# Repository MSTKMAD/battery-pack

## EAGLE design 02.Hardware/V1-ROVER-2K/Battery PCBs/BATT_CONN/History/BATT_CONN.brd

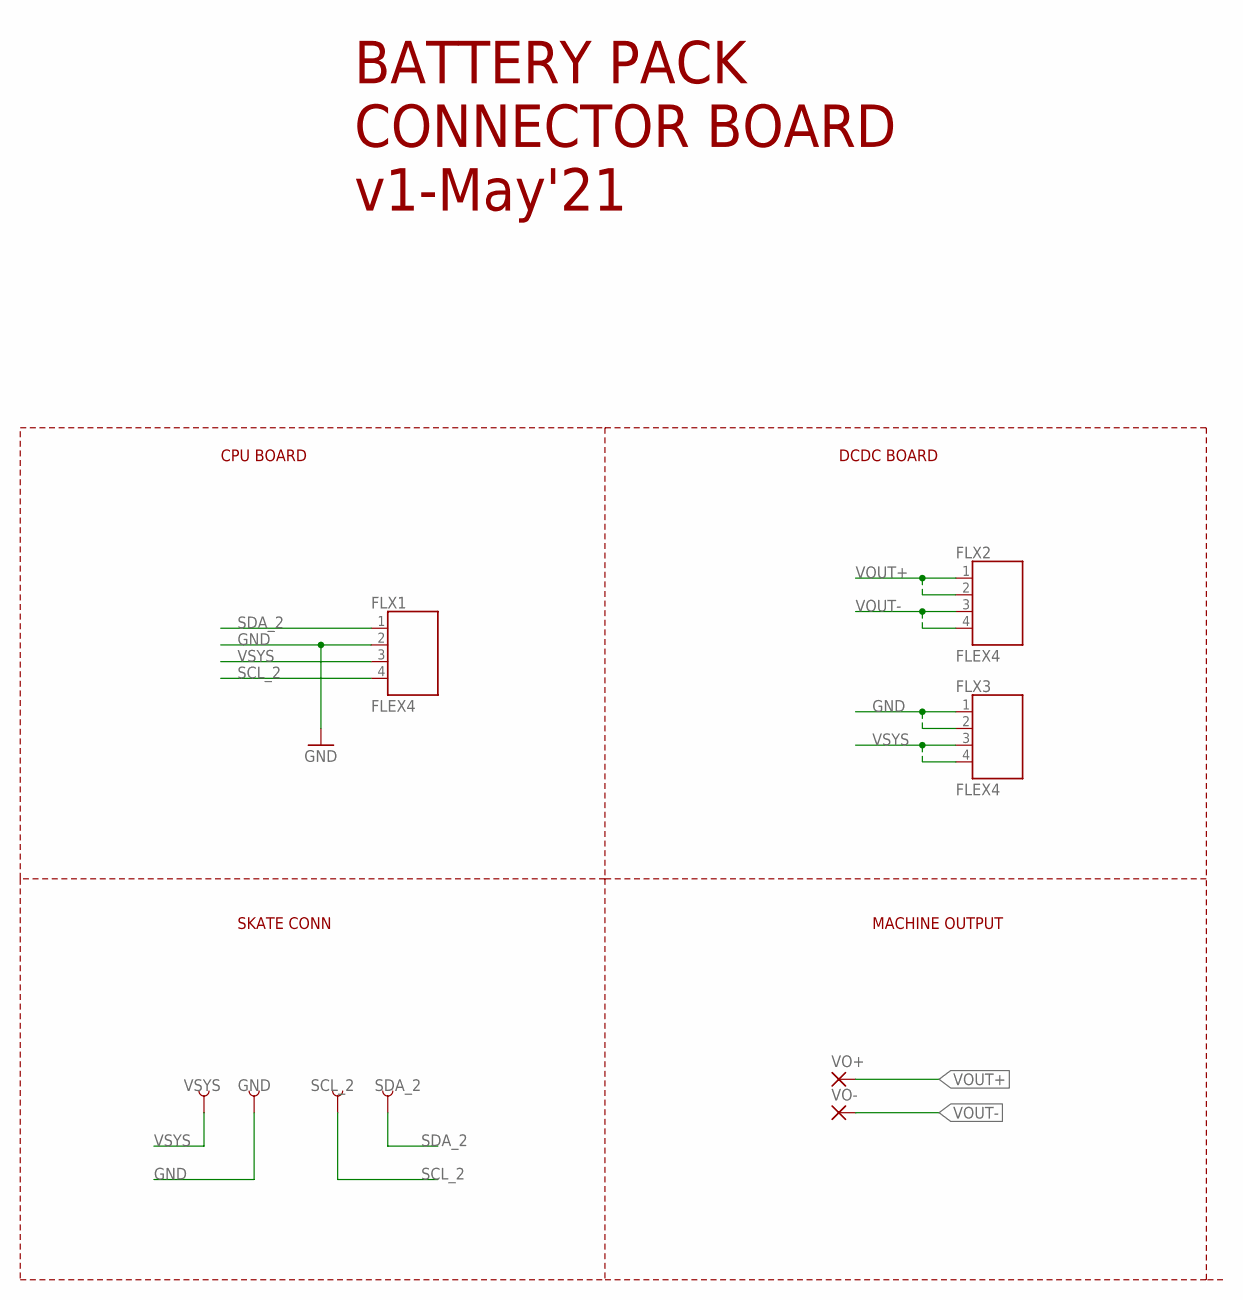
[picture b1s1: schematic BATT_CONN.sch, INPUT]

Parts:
FLX1, FLX2, FLX3: FLEX4
GND: TEST-POINT3; PAD.03X.03
SCL_2: TEST-POINT3; PAD.03X.03
SDA_2: TEST-POINT3; PAD.03X.03
VO+: SMD5; SMD2,54-5,08
VO-: SMD5; SMD2,54-5,08
VSYS: TEST-POINT3; PAD.03X.03

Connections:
GND: FLX1.2, FLX3.1, FLX3.2, GND.P$1
SCL_2: FLX1.4, SCL_2.P$1
SDA_2: FLX1.1, SDA_2.P$1
VOUT+: FLX2.1, FLX2.2, VO+.1
VOUT-: FLX2.3, FLX2.4, VO-.1
VSYS: FLX1.3, FLX3.3, FLX3.4, VSYS.P$1

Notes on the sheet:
BATTERY PACK CONNECTOR BOARD v1-May'21
CPU BOARD
DCDC BOARD
SKATE CONN
MACHINE OUTPUT

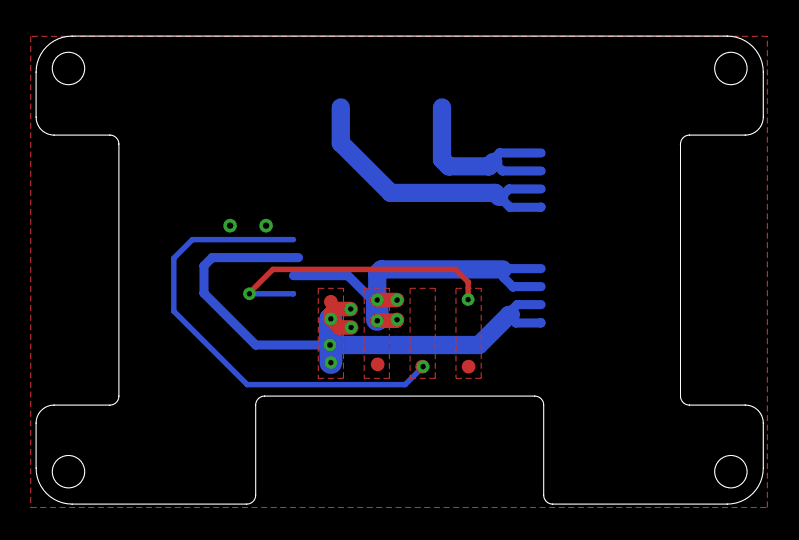
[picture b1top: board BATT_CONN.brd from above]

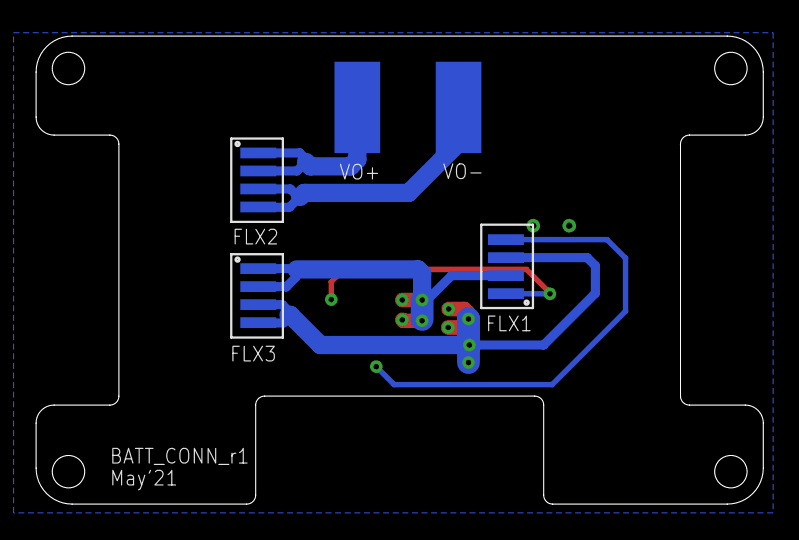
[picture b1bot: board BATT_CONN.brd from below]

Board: 2 copper layers, 40.4 x 26.0 mm, 9 parts (5 on the bottom side), 6 nets.

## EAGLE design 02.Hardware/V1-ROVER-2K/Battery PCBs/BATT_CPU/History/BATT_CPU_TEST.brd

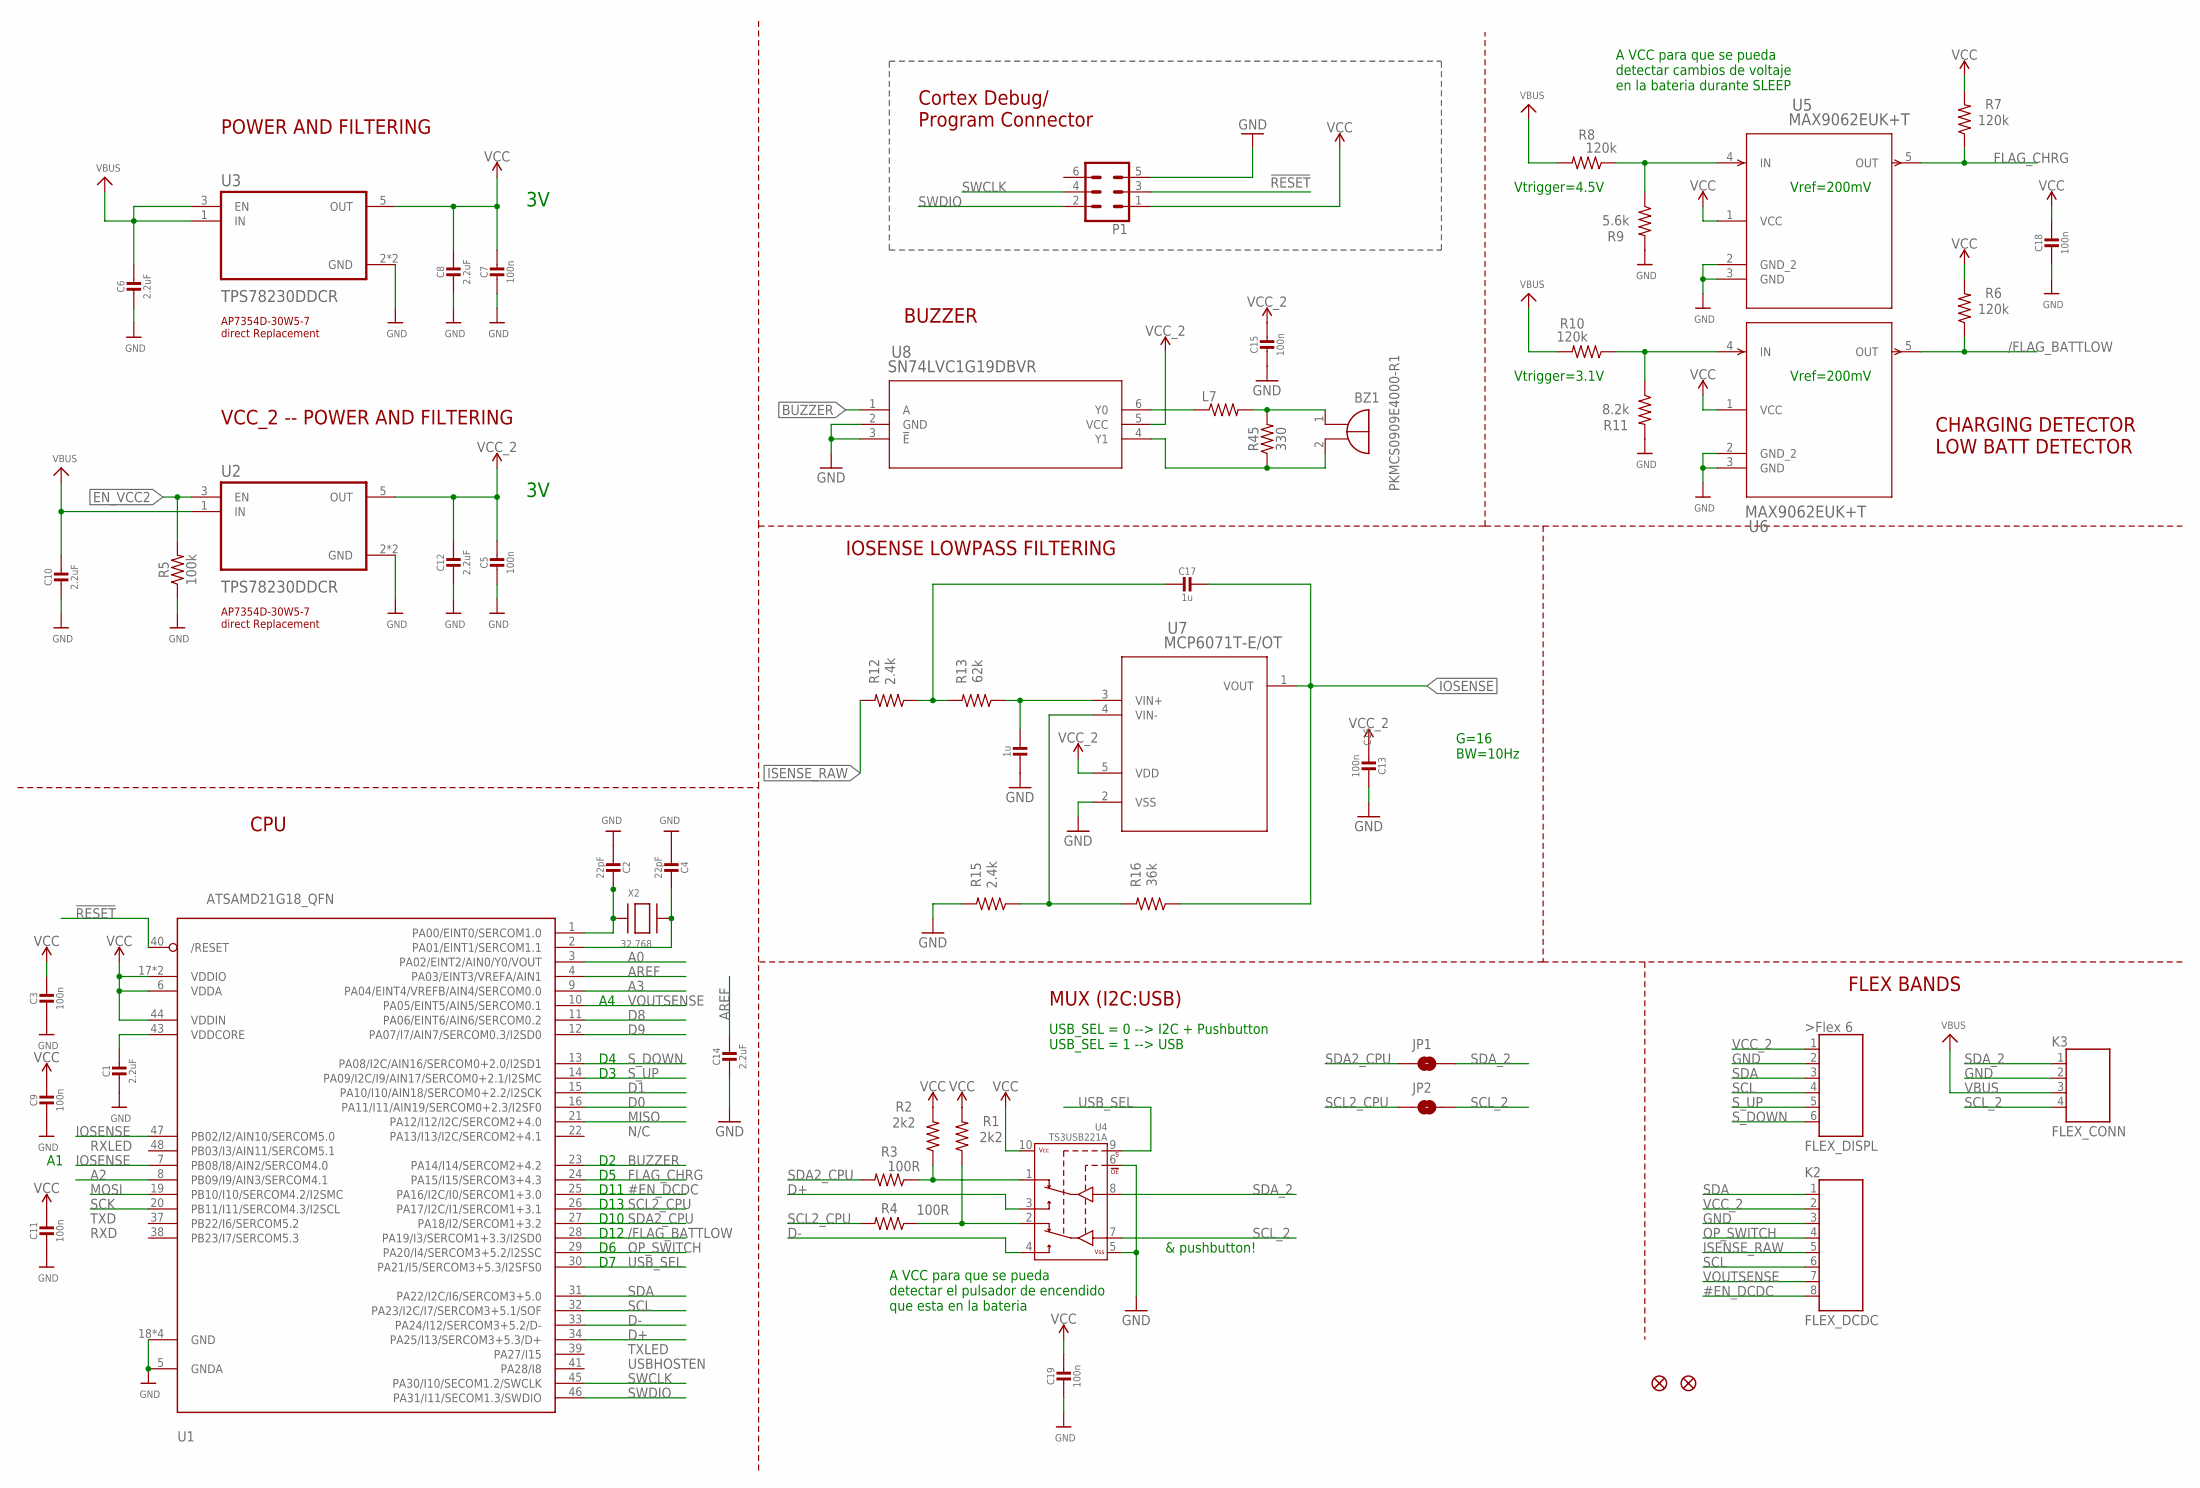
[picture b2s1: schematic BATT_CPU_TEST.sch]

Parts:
BZ1: PKMCS0909E4000-R1; PKMCS0909
C1, C14: 2.2uF; 0603-NO
C2, C4: 22pF; 0603-NO
C3, C5, C7, C9, C11, C13, C15, C18, C19: 100n; 0603-NO
C6, C8, C10, C12: 2.2uF; 0805-NO
C16, C17: 1u; 0603-NO
JP1, JP2: JUMPER-SMT_2_NO_SILK; SMT-JUMPER_2_NO_SILK
K1: FLEX_DISPL; FLEX6
K2: FLEX_DCDC; FLEX8
K3: FLEX_CONN; FLEX4
L7: MMZ2012Y202BT000; 0805
P1: CONN03X2-PROGRAM-POGO-SWD-1.27; 2X3-PROGRAM-POGO-SWD-1.27
R1, R2: 2k2; 0603
R3, R4: 100R; 0603
R5: 100k; 0603
R6, R7, R8, R10: 120k; 0603
R9: 5.6k; 0603
R11: 8.2k; 0603
R12, R15: 2.4k; 0603
R13: 62k; 0603
R16: 36k; 0603
R45: 330; 0603
U1: ATSAMD21G18_QFN; TQFN48_7MM
U2, U3: TPS78230DDCR; SOT95P280X110-5N
U4: TS3USB221A; QFN-10-RSE
U5, U6: MAX9062EUK+T; 21-0057F_MXM
U7: MCP6071T-E/OT; SOT-23-5_MC_MCH
U8: SN74LVC1G19DBVR; DBV6
U$34, U$35: FIDUCIAL""; FIDUCIAL_1MM
X2: 32.768; XTAL3215

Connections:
!RESET: P1.3, U1.40 (/RESET)
#EN_DCDC: K2.8, U1.25 (PA16/I2C/I0/SERCOM1+3.0)
/FLAG_BATTLOW: R6.1, U1.28 (PA19/I3/SERCOM1+3.3/I2SD0), U6.5 (OUT)
A0: U1.3 (PA02/EINT2/AIN0/Y0/VOUT)
A2: U1.8 (PB09/I9/AIN3/SERCOM4.1)
A3: U1.9 (PA04/EINT4/VREFB/AIN4/SERCOM0.0)
AREF: C14.1, U1.4 (PA03/EINT3/VREFA/AIN1)
BUZZER: U1.23 (PA14/I14/SERCOM2+4.2), U8.1 (A)
D0: U1.16 (PA11/I11/AIN19/SERCOM0+2.3/I2SF0)
D1: U1.15 (PA10/I10/AIN18/SERCOM0+2.2/I2SCK)
D8: U1.11 (PA06/EINT6/AIN6/SERCOM0.2)
D9: U1.12 (PA07/I7/AIN7/SERCOM0.3/I2SD0)
D+: U1.34 (PA25/I13/SERCOM3+5.3/D+), U4.3 (2D+)
D-: U1.33 (PA24/I12/SERCOM3+5.2/D-), U4.4 (2D-)
EN_VCC2: R5.2, U2.3 (EN)
FLAG_CHRG: R7.1, U1.24 (PA15/I15/SERCOM3+4.3), U5.5 (OUT)
GND: C1.2, C2.2, C3.2, C4.2, C5.2, C6.2, C7.2, C8.2, C9.2, C10.2, C11.2, C12.2, C13.2, C14.2, C15.2, C16.2, C18.2, C19.2, K1.2, K2.3, K3.2, P1.5, R5.1, R9.2, R11.2, R15.2, U1.5 (GNDA), U1.18 (GND), U1.35 (GND), U1.42 (GND), U1.THERMAL (GND), U2.2 (GND), U2.4 (GND), U3.2 (GND), U3.4 (GND), U4.5 (VSS), U4.6 (!OE), U5.2 (GND_2), U5.3 (GND), U6.2 (GND_2), U6.3 (GND), U7.2 (VSS), U8.2 (GND), U8.3 (!E)
IOSENSE: C17.2, R16.1, U1.7 (PB08/I8/AIN2/SERCOM4.0), U1.47 (PB02/I2/AIN10/SERCOM5.0), U7.1 (VOUT)
ISENSE_RAW: K2.5, R12.2
MISO: U1.21 (PA12/I12/I2C/SERCOM2+4.0)
MOSI: U1.19 (PB10/I10/SERCOM4.2/I2SMC)
unnamed: R15.1, R16.2, U7.4 (VIN-)
unnamed: R2.1, R3.1, U4.1 (1D+)
unnamed: R1.1, R4.1, U4.2 (1D-)
unnamed: C2.1, U1.1 (PA00/EINT0/SERCOM1.0), X2.P$1
unnamed: C4.1, U1.2 (PA01/EINT1/SERCOM1.1), X2.P$2
unnamed: C17.1, R12.1, R13.2
unnamed: R10.1, R11.1, U6.4 (IN)
unnamed: R8.1, R9.1, U5.4 (IN)
unnamed: C16.1, R13.1, U7.3 (VIN+)
unnamed: L7.1, U8.6 (Y0)
unnamed: BZ1.1 (+), L7.2, R45.2
unnamed: BZ1.2 (-), R45.1, U8.4 (Y1)
OP_SWITCH: K2.4, U1.29 (PA20/I4/SERCOM3+5.2/I2SSC)
SCK: U1.20 (PB11/I11/SERCOM4.3/I2SCL)
SCL: K1.4, K2.6, U1.32 (PA23/I2C/I7/SERCOM3+5.1/SOF)
SCL2_CPU: JP2.1, R4.2, U1.26 (PA17/I2C/I1/SERCOM1+3.1)
SCL_2: JP2.2, K3.4, U4.7 (D-)
SDA: K1.3, K2.1, U1.31 (PA22/I2C/I6/SERCOM3+5.0)
SDA2_CPU: JP1.1, R3.2, U1.27 (PA18/I2/SERCOM1+3.2)
SDA_2: JP1.2, K3.1, U4.8 (D+)
SWCLK: P1.4, U1.45 (PA30/I10/SECOM1.2/SWCLK)
SWDIO: P1.2, U1.46 (PA31/I11/SECOM1.3/SWDIO)
S_DOWN: K1.6, U1.13 (PA08/I2C/AIN16/SERCOM0+2.0/I2SD1)
S_UP: K1.5, U1.14 (PA09/I2C/I9/AIN17/SERCOM0+2.1/I2SMC)
USB_SEL: U1.30 (PA21/I5/SERCOM3+5.3/I2SFS0), U4.9 (S)
VBUS: C6.1, C10.1, K3.3, R8.2, R10.2, U2.1 (IN), U3.1 (IN), U3.3 (EN)
VCC: C3.1, C7.1, C8.1, C9.1, C11.1, C18.1, C19.1, P1.1, R1.2, R2.2, R6.2, R7.2, U1.6 (VDDA), U1.17 (VDDIO), U1.36 (VDDIO), U1.44 (VDDIN), U3.5 (OUT), U4.10 (VCC), U5.1 (VCC), U6.1 (VCC)
VCC_2: C5.1, C12.1, C13.1, C15.1, K1.1, K2.2, U2.5 (OUT), U7.5 (VDD), U8.5 (VCC)
VDDCORE: C1.1, U1.43 (VDDCORE)
VOUTSENSE: K2.7, U1.10 (PA05/EINT5/AIN5/SERCOM0.1)

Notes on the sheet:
POWER AND FILTERING
N/C
TXLED
USBHOSTEN
RXLED
TXD
RXD
Cortex Debug/ Program Connector
BUZZER
AP7354D-30W5-7 direct Replacement
VCC_2 -- POWER AND FILTERING
A VCC para que se pueda detectar el pulsador de encendido que esta en la bateria
D10
A VCC para que se pueda detectar cambios de voltaje en la bateria durante SLEEP
G=16 BW=10Hz
IOSENSE LOWPASS FILTERING
FLEX BANDS
MUX (I2C:USB)
CHARGING DETECTOR LOW BATT DETECTOR
CPU
Vref=200mV
Vtrigger=4.5V
Vtrigger=3.1V
D13
D11
USB_SEL = 0 --> I2C + Pushbutton USB_SEL = 1 --> USB
& pushbutton!
D12

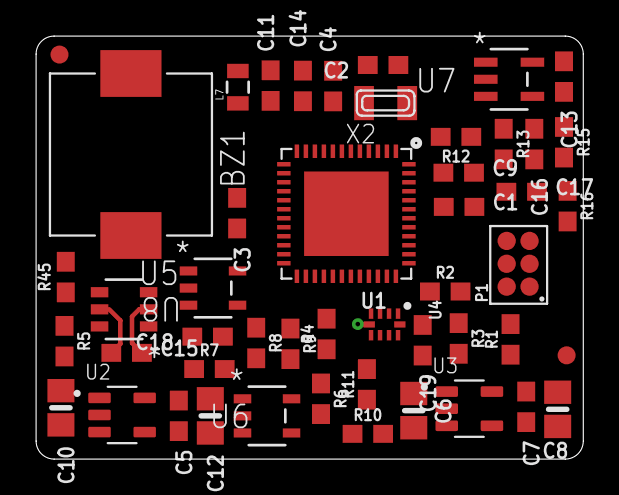
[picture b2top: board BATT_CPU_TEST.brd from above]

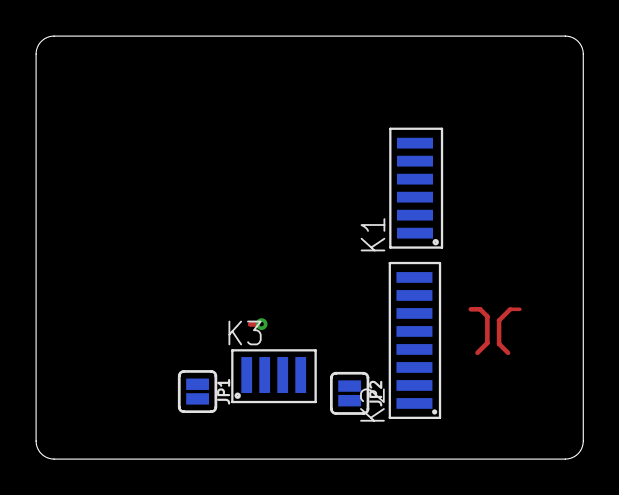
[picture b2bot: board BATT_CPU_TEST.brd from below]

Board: 4 copper layers, 30.4 x 23.5 mm, 54 parts (5 on the bottom side), 41 nets.

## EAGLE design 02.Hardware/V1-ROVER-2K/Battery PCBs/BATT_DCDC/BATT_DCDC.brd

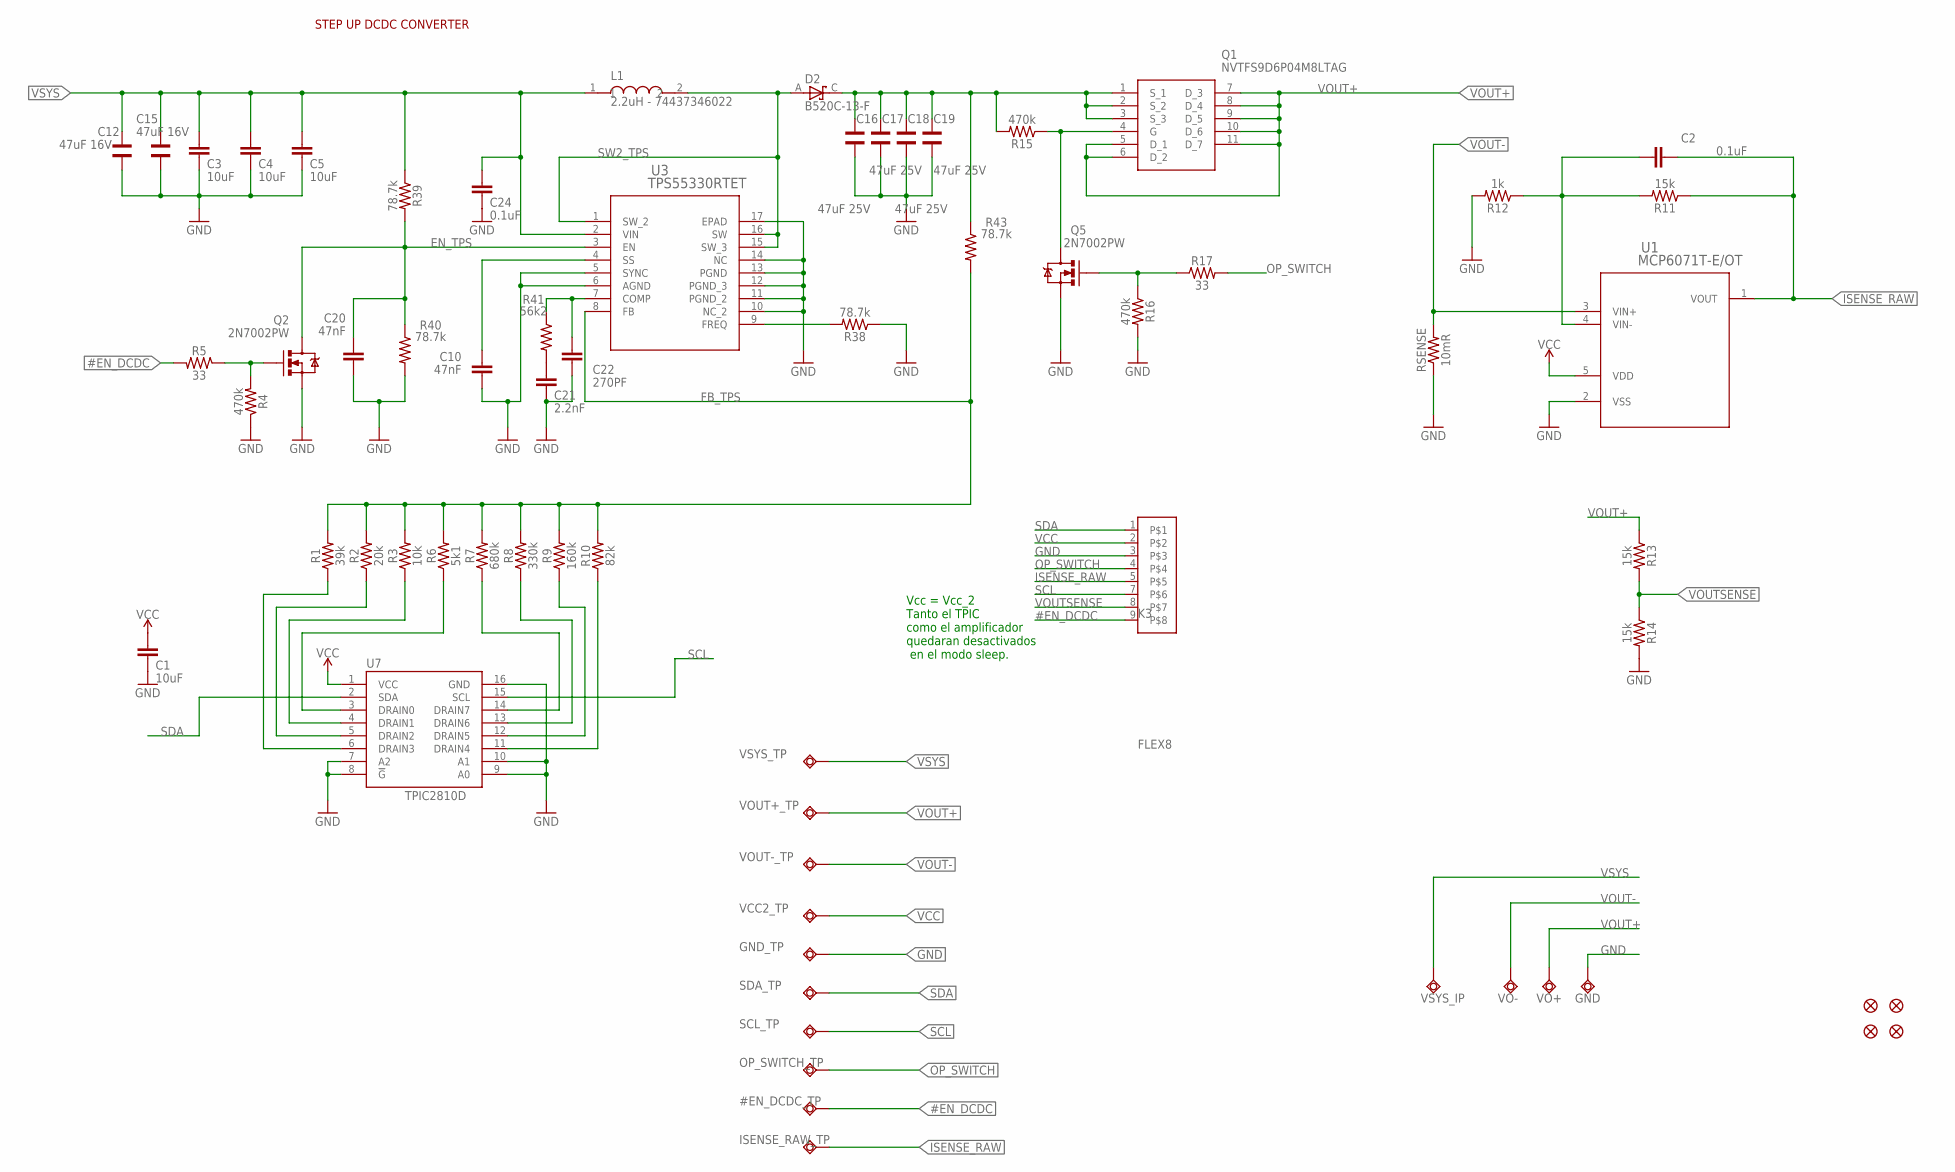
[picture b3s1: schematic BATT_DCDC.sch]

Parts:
#EN_DCDC_TP: TESTPAD_TPSQB1,27; TESTPAD_B1,27
C1, C3, C4, C5: 10uF; 0805
C2, C24: 0.1uF; 0603
C10, C20: 47nF; 0603
C12, C15: 47uF 16V; WCAP-CSGP_1210
C16, C17, C18, C19: 47uF 25V; WCAP-CSGP_1210
C21: 2.2nF; 0603
C22: 270PF; 0603
D2: B520C-13-F; DIOM7959X250N
GND: TESTPAD_TPSQTP15SQ; TESTPAD_TP15SQ
GND_TP: TESTPAD_TPSQB1,27; TESTPAD_B1,27
ISENSE_RAW_TP: TESTPAD_TPSQB1,27; TESTPAD_B1,27
K3: FLEX8
L1: 2.2uH - 74437346022; INDM7366X500
OP_SWITCH_TP: TESTPAD_TPSQB1,27; TESTPAD_B1,27
Q1: NVTFS9D6P04M8LTAG; NVTFS5124PLTWG
Q2, Q5: 2N7002PW; SOT323
R1: 39k; 0402
R2: 20k; 0402
R3: 10k; 0402
R4, R15, R16: 470k; 0402
R5, R17: 33; 0402
R6: 5k1; 0402
R7: 680k; 0402
R8: 330k; 0402
R9: 160k; 0402
R10: 82k; 0402
R11, R13, R14: 15k; 0402
R12: 1k; 0402
R38, R39, R40, R43: 78.7k; 0402
R41: 56k2; 0402
RSENSE: 10mR; 0603
SCL_TP: TESTPAD_TPSQB1,27; TESTPAD_B1,27
SDA_TP: TESTPAD_TPSQB1,27; TESTPAD_B1,27
U1: MCP6071T-E/OT; SOT-23-5_MC_MCH
U3: TPS55330RTET; RTE16_1P66X1P66_TEX
U7: TPIC2810D; SO16
U$1, U$2, U$34, U$35: FIDUCIAL""; FIDUCIAL_1MM
VCC2_TP: TESTPAD_TPSQB1,27; TESTPAD_B1,27
VO+: TESTPAD_TPSQTP15SQ; TESTPAD_TP15SQ
VO-: TESTPAD_TPSQTP15SQ; TESTPAD_TP15SQ
VOUT+_TP: TESTPAD_TPSQB1,27; TESTPAD_B1,27
VOUT-_TP: TESTPAD_TPSQB1,27; TESTPAD_B1,27
VSYS_IP: TESTPAD_TPSQTP15SQ; TESTPAD_TP15SQ
VSYS_TP: TESTPAD_TPSQB1,27; TESTPAD_B1,27

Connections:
#EN_DCDC: #EN_DCDC_TP.TP, K3.9, R5.2
COMP_TPS: C22.2, R41.1, U3.7 (COMP)
EN_TPS: C20.1, Q2.3 (D), R39.2, R40.1, U3.3 (EN)
FB_TPS: R1.2, R2.2, R3.2, R6.2, R7.2, R8.2, R9.2, R10.2, R43.2, U3.8 (FB)
FREQ_TPS: R38.2, U3.9 (FREQ)
GND: C1.1, C3.1, C4.1, C5.1, C10.2, C12.1, C15.1, C16.1, C17.1, C18.1, C19.1, C20.2, C21.1, C22.1, C24.1, GND.TP, GND_TP.TP, K3.3, Q2.2 (S), Q5.2 (S), R4.1, R12.2, R14.2, R16.2, R38.1, R40.2, RSENSE.1, U1.2 (VSS), U3.5 (SYNC), U3.6 (AGND), U3.10 (NC_2), U3.11 (PGND_2), U3.12 (PGND_3), U3.13 (PGND), U3.14 (NC), U3.17 (EPAD), U7.7 (A2), U7.8 (!G), U7.9 (A0), U7.10 (A1), U7.16 (GND)
ISENSE_RAW: C2.1, ISENSE_RAW_TP.TP, K3.5, R11.1, U1.1 (VOUT)
unnamed: C2.2, R11.2, R12.1, U1.4 (VIN-)
unnamed: R1.1, U7.6 (DRAIN3)
unnamed: R2.1, U7.5 (DRAIN2)
unnamed: Q2.1 (G), R4.2, R5.1
unnamed: R3.1, U7.4 (DRAIN1)
unnamed: R6.1, U7.3 (DRAIN0)
unnamed: R7.1, U7.14 (DRAIN7)
unnamed: Q1.4 (G), Q5.3 (D), R15.1
unnamed: R8.1, U7.13 (DRAIN6)
unnamed: R9.1, U7.12 (DRAIN5)
unnamed: R10.1, U7.11 (DRAIN4)
unnamed: Q5.1 (G), R16.1, R17.1
unnamed: C10.1, U3.4 (SS)
unnamed: C21.2, R41.2
OP_SWITCH: K3.4, OP_SWITCH_TP.TP, R17.2
SCL: K3.7, SCL_TP.TP, U7.15 (SCL)
SDA: K3.1, SDA_TP.TP, U7.2 (SDA)
SW2_TPS: D2.A, L1.2, U3.1 (SW_2), U3.15 (SW_3), U3.16 (SW)
VCC: C1.2, K3.2, U1.5 (VDD), U7.1 (VCC), VCC2_TP.TP
VOUT+: Q1.5 (D_1), Q1.6 (D_2), Q1.7 (D_3), Q1.8 (D_4), Q1.9 (D_5), Q1.10 (D_6), Q1.11 (D_7), R13.1, VO+.TP, VOUT+_TP.TP
VOUT-: RSENSE.2, U1.3 (VIN+), VO-.TP, VOUT-_TP.TP
VOUTSENSE: K3.8, R13.2, R14.1
VSOURCE: C16.2, C17.2, C18.2, C19.2, D2.C, Q1.1 (S_1), Q1.2 (S_2), Q1.3 (S_3), R15.2, R43.1
VSYS: C3.2, C4.2, C5.2, C12.2, C15.2, C24.2, L1.1, R39.1, U3.2 (VIN), VSYS_IP.TP, VSYS_TP.TP

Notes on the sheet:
STEP UP DCDC CONVERTER
Vcc = Vcc_2 Tanto el TPIC como el amplificador quedaran desactivados en el modo sleep.

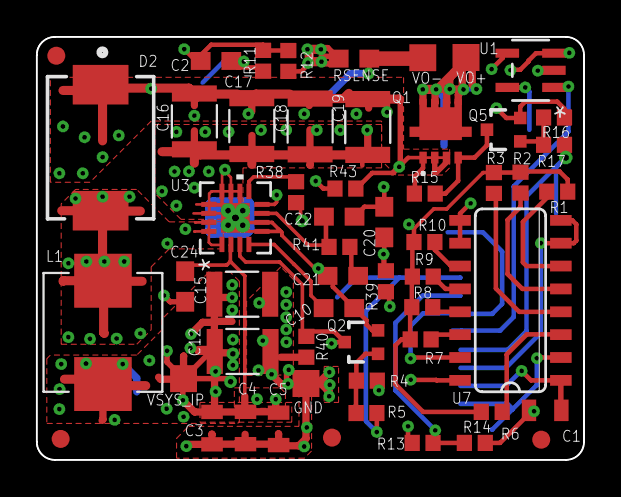
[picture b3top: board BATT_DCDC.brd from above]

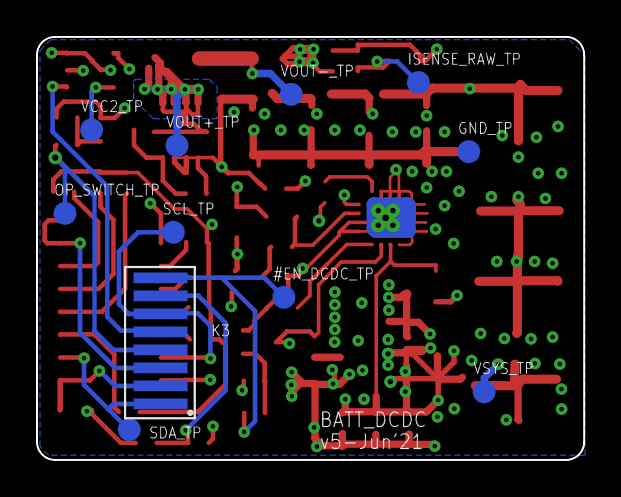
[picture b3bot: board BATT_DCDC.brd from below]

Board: 4 copper layers, 30.4 x 23.5 mm, 66 parts (11 on the bottom side), 31 nets.

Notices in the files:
parts and their libraries:
SparkFun-Aesthetics: Licensing: Creative Commons ShareAlike 4.0 International - https://creativecommons.org/licenses/by-sa/4.0
microbuilder: This work is placed in the public domain, and may be freely used for commercial and non-commercial work with the following conditions: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
